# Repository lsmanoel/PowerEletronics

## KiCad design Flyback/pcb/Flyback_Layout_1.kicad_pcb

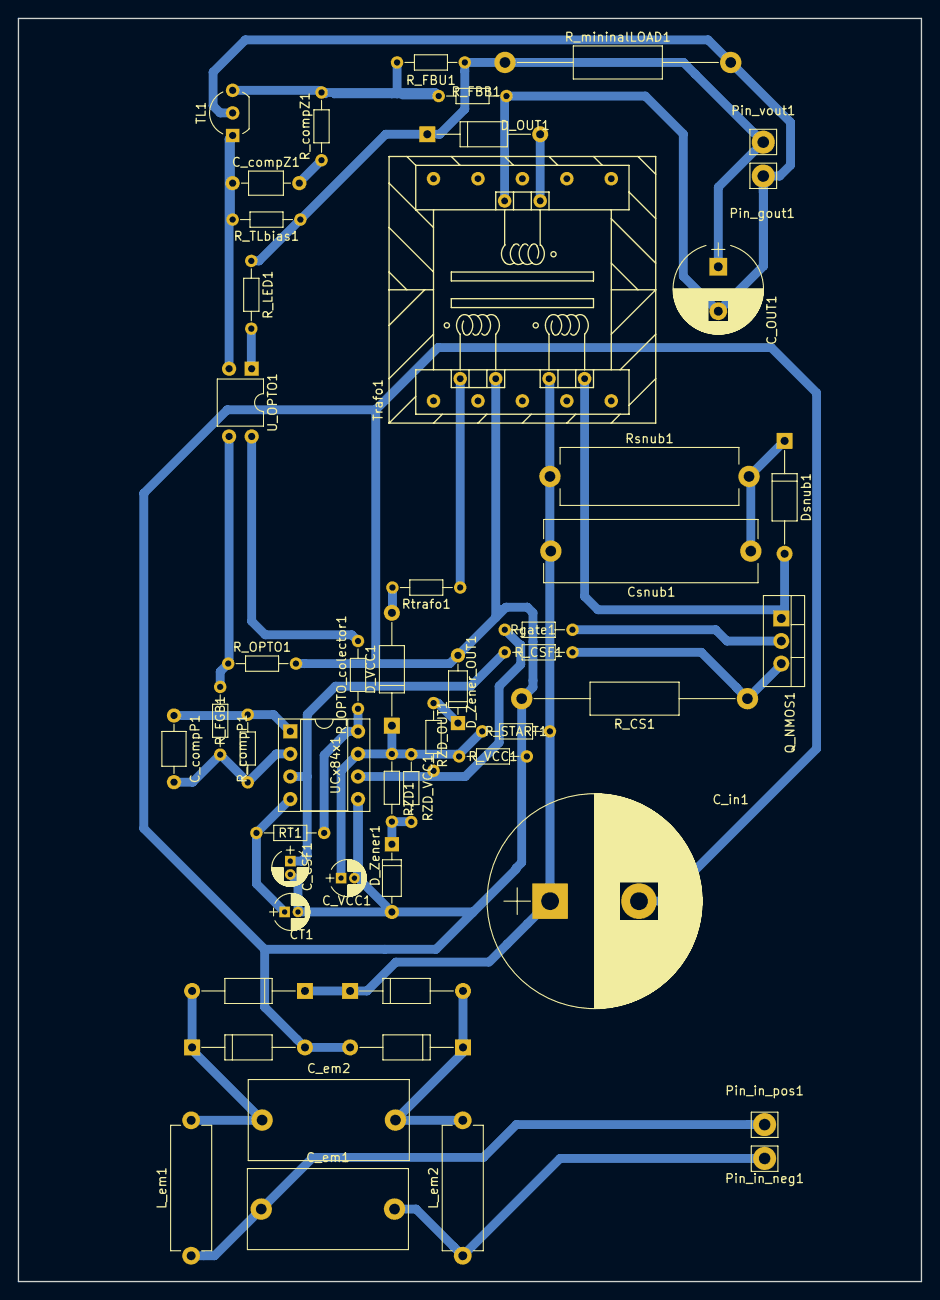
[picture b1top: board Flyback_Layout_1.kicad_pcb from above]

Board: 2 copper layers, 101.6 x 142.1 mm, 51 parts (0 on the bottom side), 30 nets.

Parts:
CT1: C; CP_Radial_D4.0mm_P1.50mm
C_CSF1: C; CP_Radial_D4.0mm_P1.50mm
C_OUT1: C; CP_Radial_D10.0mm_P5.00mm
C_VCC1: C; CP_Radial_D4.0mm_P1.50mm
C_compP1: C; C_Axial_L3.8mm_D2.6mm_P7.50mm_Horizontal
C_compZ1: C; C_Axial_L3.8mm_D2.6mm_P7.50mm_Horizontal
C_em1, C_em2: C; C_Rect_L18.0mm_W9.0mm_P15.00mm_FKS3_FKP3
C_in1: 150uF; CP_Radial_D24.0mm_P10.00mm_SnapIn
Csnub1: C; C_Rect_L24.0mm_W7.0mm_P22.50mm_MKT
D_OUT1: D; D_A-405_P12.70mm_Horizontal
D_VCC1: D; D_A-405_P12.70mm_Horizontal
D_Zener1: 18V; D_DO-35_SOD27_P7.62mm_Horizontal
D_Zener_OUT1: 12V; D_DO-35_SOD27_P7.62mm_Horizontal
Dret_1, Dret_2, Dret_3, Dret_4: D; D_A-405_P12.70mm_Horizontal
Dsnub1: D; D_A-405_P12.70mm_Horizontal
L_em1, L_em2: L; L_Axial_L14.0mm_D4.5mm_P15.24mm_Horizontal_Fastron_LACC
Pin_gout1: CONN_01X01; Pin_d1.4mm_L8.5mm_W2.8mm_FlatFork
Pin_in_neg1: CONN_01X01; Pin_d1.4mm_L8.5mm_W2.8mm_FlatFork
Pin_in_pos1: CONN_01X01; Pin_d1.4mm_L8.5mm_W2.8mm_FlatFork
Pin_vout1: CONN_01X01; Pin_d1.4mm_L8.5mm_W2.8mm_FlatFork
Q_NMOS1: Q_NMOS_DGS; TO-220-3_Vertical
RT1: R; R_Axial_DIN0204_L3.6mm_D1.6mm_P7.62mm_Horizontal
RZD1: R; R_Axial_DIN0204_L3.6mm_D1.6mm_P7.62mm_Horizontal
RZD_OUT1: R; R_Axial_DIN0204_L3.6mm_D1.6mm_P7.62mm_Horizontal
RZD_VCC1: R; R_Axial_DIN0204_L3.6mm_D1.6mm_P7.62mm_Horizontal
R_CS1: R; R_Axial_DIN0411_L9.9mm_D3.6mm_P25.40mm_Horizontal
R_CSF1: R; R_Axial_DIN0204_L3.6mm_D1.6mm_P7.62mm_Horizontal
R_FBB1: R; R_Axial_DIN0204_L3.6mm_D1.6mm_P7.62mm_Horizontal
R_FBU1: R; R_Axial_DIN0204_L3.6mm_D1.6mm_P7.62mm_Horizontal
R_FGB1: R; R_Axial_DIN0204_L3.6mm_D1.6mm_P7.62mm_Horizontal
R_LED1: R; R_Axial_DIN0204_L3.6mm_D1.6mm_P7.62mm_Horizontal
R_OPTO1: R; R_Axial_DIN0204_L3.6mm_D1.6mm_P7.62mm_Horizontal
R_OPTO_colector1: R; R_Axial_DIN0204_L3.6mm_D1.6mm_P7.62mm_Horizontal
R_START1: R; R_Axial_DIN0204_L3.6mm_D1.6mm_P7.62mm_Horizontal
R_TLbias1: R; R_Axial_DIN0204_L3.6mm_D1.6mm_P7.62mm_Horizontal
R_VCC1: R; R_Axial_DIN0204_L3.6mm_D1.6mm_P7.62mm_Horizontal
R_compP1: R; R_Axial_DIN0204_L3.6mm_D1.6mm_P7.62mm_Horizontal
R_compZ1: R; R_Axial_DIN0204_L3.6mm_D1.6mm_P7.62mm_Horizontal
R_mininalLOAD1: R; R_Axial_DIN0411_L9.9mm_D3.6mm_P25.40mm_Horizontal
Rgate1: R; R_Axial_DIN0204_L3.6mm_D1.6mm_P7.62mm_Horizontal
Rsnub1: R; R_Axial_Power_L20.0mm_W6.4mm_P22.40mm
Rtrafo1: R; R_Axial_DIN0204_L3.6mm_D1.6mm_P7.62mm_Horizontal
TL1: Ajus_Shunt; TO-92_Inline_Wide
Trafo1: Transformer_1P_2S; core_30-7
UCx84x1: DIL8; DIP-8_W7.62mm_Socket
U_OPTO1: OPTO; DIP-4_W7.62mm

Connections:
COMP: C_compP1.1, R_compP1.2, UCx84x1.1
DRENO: Dsnub1.2, Q_NMOS1.1, Trafo1.2
GATE: Q_NMOS1.2, Rgate1.2
GND: CT1.2, C_CSF1.2, C_VCC1.2, C_in1.2, D_Zener1.2, D_Zener_OUT1.2, Dret_1.2, Dret_3.2, R_CS1.2, R_OPTO1.2, R_VCC1.2, Trafo1.6, UCx84x1.5
GOUT: C_OUT1.2, Pin_gout1.1, R_FBB1.1, R_mininalLOAD1.2, TL1.2, Trafo1.4
ISENSE: C_CSF1.1, R_CSF1.2, UCx84x1.3
unnamed: C_compZ1.1, R_TLbias1.2, TL1.1, U_OPTO1.2
unnamed: C_compZ1.2, R_compZ1.1
unnamed: C_em1.1, L_em1.1, Pin_in_pos1.1
unnamed: C_em1.2, L_em2.1, Pin_in_neg1.1
unnamed: C_em2.1, Dret_1.1, Dret_2.2, L_em1.2
unnamed: C_em2.2, Dret_3.1, Dret_4.2, L_em2.2
unnamed: Csnub1.2, Dsnub1.1, Rsnub1.2
unnamed: D_VCC1.2, Rtrafo1.2
unnamed: D_Zener1.1, RZD1.2, RZD_VCC1.2
unnamed: D_Zener_OUT1.1, RZD_OUT1.2
unnamed: Q_NMOS1.3, R_CS1.1, R_CSF1.1
unnamed: R_FBB1.2, R_FBU1.1, R_compZ1.2, TL1.3
unnamed: R_FGB1.2, R_OPTO1.1, U_OPTO1.3
unnamed: R_LED1.2, U_OPTO1.1
unnamed: R_OPTO_colector1.2, U_OPTO1.4
unnamed: Rtrafo1.1, Trafo1.5
OUTPUT: RZD_OUT1.1, Rgate1.1, UCx84x1.6
RTCT: CT1.1, RT1.2, UCx84x1.4
VCC: C_VCC1.1, D_VCC1.1, RZD1.1, RZD_VCC1.1, R_START1.2, R_VCC1.1, UCx84x1.7
VFB: C_compP1.2, R_FGB1.1, R_compP1.1, UCx84x1.2
VOUT: C_OUT1.1, D_OUT1.1, Pin_vout1.1, R_FBU1.2, R_LED1.1, R_TLbias1.1, R_mininalLOAD1.1
VREF: RT1.1, R_OPTO_colector1.1, UCx84x1.8
VRET: C_in1.1, Csnub1.1, Dret_2.1, Dret_4.1, R_START1.1, Rsnub1.1, Trafo1.1
Vtrafo: D_OUT1.2, Trafo1.3

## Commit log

2019-02-24 Created using Colaboratory
2019-02-24 image add
2019-02-25 Figuras dos valores de simulação
2019-02-25 add slide
2019-02-25 image update
2019-02-25 Smath e versão html
2019-02-25 Calculos dos diodos (sem a pasta das figuras)
2019-02-25 Calculos image
2019-02-26 add figure
2019-02-27 html add
2019-03-11 cap - buck circuit image add
2019-03-12 update cap section
2019-03-14 Diodo e mosfet imagens
2019-03-14 add simulation
2019-03-14 add html
2019-03-25 add driver section
2019-03-25 add circuit image
2019-03-27 add lm3485 data images
2019-03-28 add tps_40056
2019-03-28 add layout section
2019-03-28 images add
2019-03-31 add artigo revisao
2019-03-31 add image - layout section
2019-04-05 git status!
2019-05-30 Planilha
2019-05-30 datasheet
2019-05-30 files
2019-05-30 add pdf
2019-05-30 spice
2019-05-30 add simulation folder
2019-05-30 simulation add - no work
2019-06-01 comita
2019-06-01 planiha update
2019-06-01 App notes
2019-06-05 new app notes, planilha update
2019-06-06 UpUpUpdatetete
2019-06-07 planilha texas
2019-06-07 planilha excel texas
2019-06-09 planilha updade, pdf flyback
2019-06-10 simulação valores da planilha e datasheet
2019-06-12 make layout
2019-06-12 sch finish
2019-06-13 test simulation add
2019-06-13 update simulation
2019-06-14 open and closed loop stable simulation
2019-06-15 arquivos txt com medidas
2019-06-15 (...)layout(...)
2019-06-15 layout ...
2019-06-16 simulação estável, calculo trafo
2019-06-19 git add img/!
2019-06-21 footprit ...
2019-07-09 add photo
2019-07-09 relatorio e planilha pdf
